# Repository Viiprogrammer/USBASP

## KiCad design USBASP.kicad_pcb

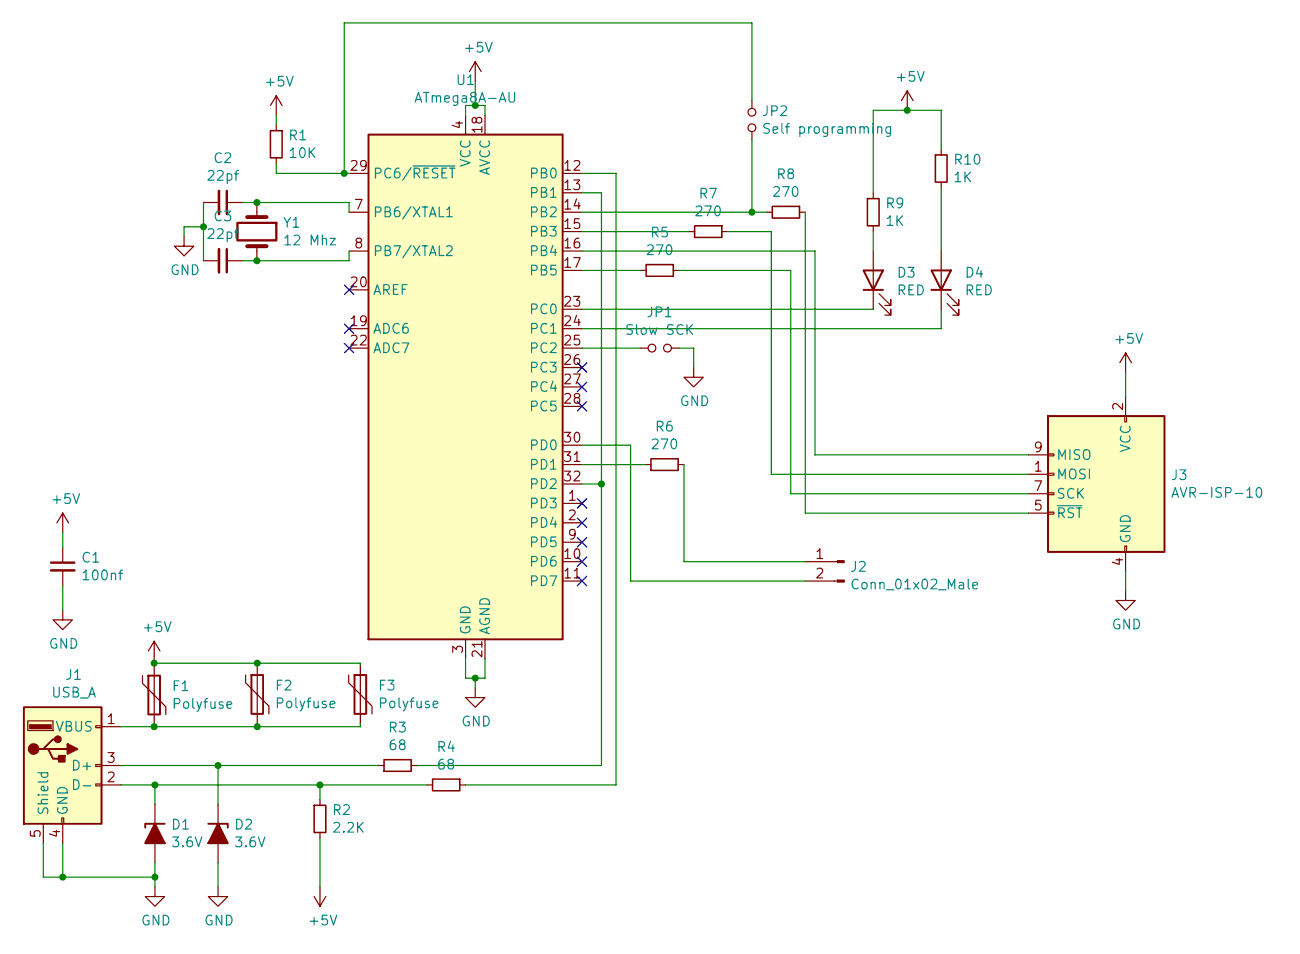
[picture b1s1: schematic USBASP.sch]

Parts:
C1: 100nf; C_1206_3216Metric
C2, C3: 22pf; C_1206_3216Metric
D1, D2: 3.6V; D_1206_3216Metric
D3, D4: RED; LED_1206_3216Metric
F1: Polyfuse; Fuse_1206_3216Metric
F2: Polyfuse; Fuse_2010_5025Metric
F3: Polyfuse; Fuse_2920_7451Metric
J1: USB_A
J2: Conn_01x02_Male; PinHeader_1x02_P2.54mm_Vertical
J3: AVR-ISP-10; PinSocket_2x05_P2.54mm_Vertical
JP1: Slow SCK; PinHeader_1x02_P2.54mm_Vertical
JP2: Self programming; PinHeader_1x02_P2.54mm_Vertical
R1: 10K; R_1206_3216Metric
R2: 2.2K; R_1206_3216Metric
R3, R4: 68; R_1206_3216Metric
R5, R6, R7, R8: 270; R_1206_3216Metric
R9, R10: 1K; R_1206_3216Metric
U1: ATmega8A-AU; TQFP-32_7x7mm_P0.8mm
Y1: 12 Mhz; Crystal_HC49-4H_Vertical

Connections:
+5V: C1.1, F1.1, F2.1, F3.1, J3.2 (VCC), R1.1, R2.2, R9.1, R10.1, U1.4 (VCC), U1.6 (VCC), U1.18 (AVCC)
GND: C1.2, C2.2, C3.2, D1.2 (A), D2.2 (A), J1.4 (GND), J1.5 (Shield), J3.4 (GND), J3.6 (GND), J3.8 (GND), J3.10 (GND), JP1.2, U1.3 (GND), U1.5 (GND), U1.21 (AGND)
unnamed: C2.1, U1.7 (PB6/XTAL1), Y1.1
unnamed: C3.1, U1.8 (PB7/XTAL2), Y1.2
unnamed: D1.1 (K), J1.2 (D-), R2.1, R4.2
unnamed: D2.1 (K), J1.3 (D+), R3.1
unnamed: D3.1 (K), U1.23 (PC0)
unnamed: D3.2 (A), R9.2
unnamed: D4.1 (K), U1.24 (PC1)
unnamed: D4.2 (A), R10.2
unnamed: F1.2, F2.2, F3.2, J1.1 (VBUS)
unnamed: J2.1, R6.2
unnamed: J2.2, U1.30 (PD0)
unnamed: J3.1 (MOSI), R7.1
unnamed: J3.5 (~RST), R8.1
unnamed: J3.7 (SCK), R5.1
unnamed: J3.9 (MISO), U1.16 (PB4)
unnamed: JP1.1, U1.25 (PC2)
unnamed: JP2.1, R8.2, U1.14 (PB2)
unnamed: JP2.2, R1.2, U1.29 (PC6/~RESET)
unnamed: R3.2, U1.13 (PB1), U1.32 (PD2)
unnamed: R4.1, U1.12 (PB0)
unnamed: R5.2, U1.17 (PB5)
unnamed: R6.1, U1.31 (PD1)
unnamed: R7.2, U1.15 (PB3)

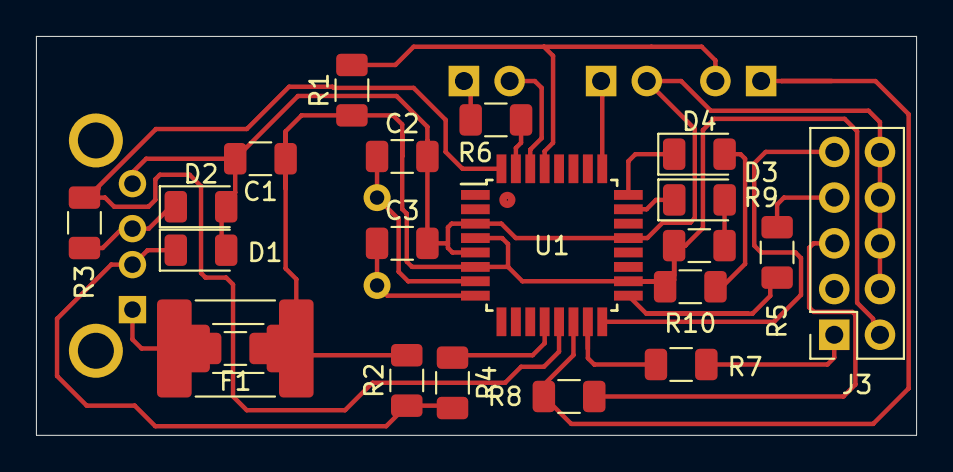
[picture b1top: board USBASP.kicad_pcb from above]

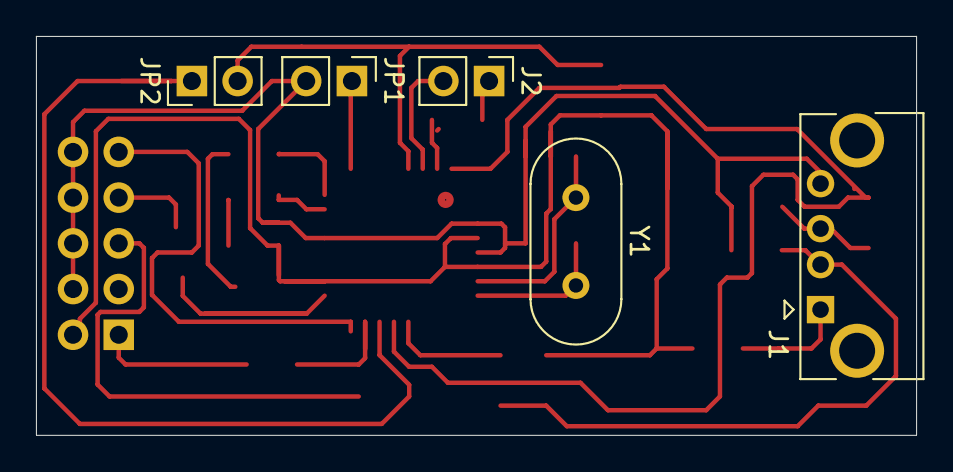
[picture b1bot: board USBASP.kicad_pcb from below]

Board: 2 copper layers, 48.9 x 22.2 mm, 27 parts (5 on the bottom side), 25 nets.

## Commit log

2020-12-04 Adding kikad content
2022-02-11 Added bom
